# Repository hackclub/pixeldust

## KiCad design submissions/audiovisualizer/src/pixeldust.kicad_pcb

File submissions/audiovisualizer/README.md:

---
name: "Hridya Agrawal"
slack_id: "U0842GMRJKC"
github_handle: "@hridaya423"
---

# Audio Visualizer

⚠️ I would like to have 120 leds for the audio visualizer, so I would need a soldering iron.

Wokwi link: https://wokwi.com/projects/428497544685566977

This PCB captures audio from an I2S microphone and displays the frequency spectrum on a 120-LEDs. It uses FFT to adjust the LED brightness based on the audio data.

## BOM

| Comment           | Footprint                                      | Quantity 
|-------------------|------------------------------------------------|----------|
| WS2812B           | LED_SMD:LED_WS2812B_PLCC4_5.0x5.0mm_P3.2mm     | 120      |
| ICS-43434         | Sensor_Audio:InvenSense_ICS-43434-6_3.5x2.65mm | 1        |
| XIAO-RP2040-DIP   |Seeed Studio XIAO Series Library:XIAO-RP2040-DIP| 1        |

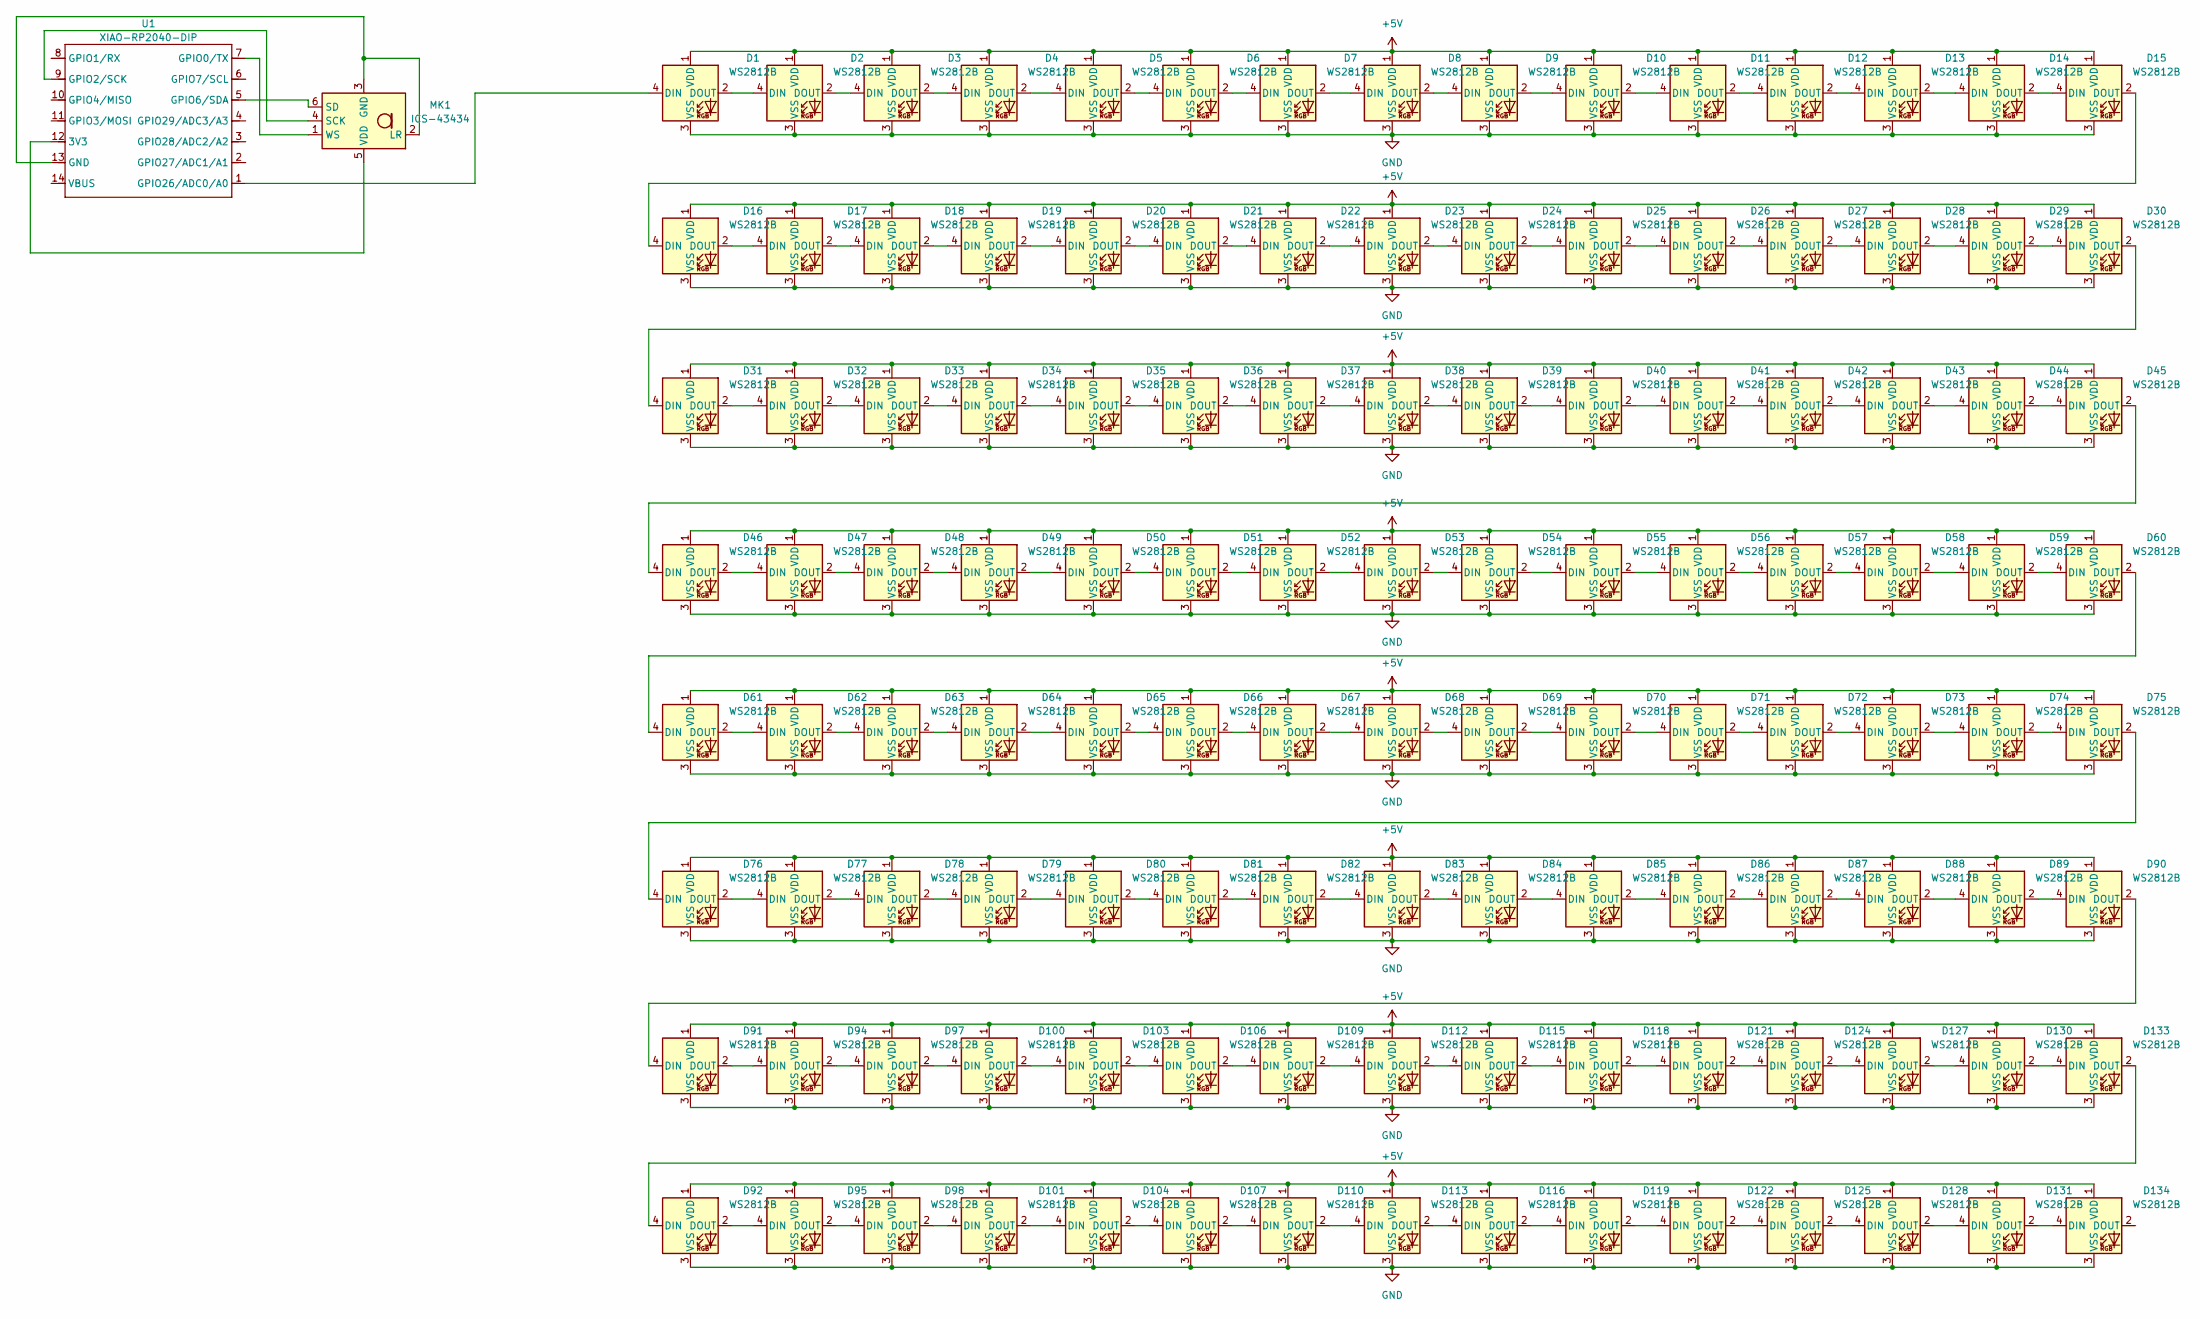
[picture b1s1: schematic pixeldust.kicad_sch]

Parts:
D1, D2, D3, D4, D5, D6, D7, D8, D9, D10, D11, D12, D13, D14, D15, D16, D17, D18, D19, D20, D21, D22, D23, D24, D25, D26, D27, D28, D29, D30, D31, D32, D33, D34, D35, D36, D37, D38, D39, D40, D41, D42, D43, D44, D45, D46, D47, D48, D49, D50, D51, D52, D53, D54, D55, D56, D57, D58, D59, D60, D61, D62, D63, D64, D65, D66, D67, D68, D69, D70, D71, D72, D73, D74, D75, D76, D77, D78, D79, D80, D81, D82, D83, D84, D85, D86, D87, D88, D89, D90, D91, D92, D94, D95, D97, D98, D100, D101, D103, D104, D106, D107, D109, D110, D112, D113, D115, D116, D118, D119, D121, D122, D124, D125, D127, D128, D130, D131, D133, D134: WS2812B; LED_WS2812B_PLCC4_5.0x5.0mm_P3.2mm
MK1: ICS-43434; InvenSense_ICS-43434-6_3.5x2.65mm
U1: XIAO-RP2040-DIP

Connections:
+5V: D1.1 (VDD), D2.1 (VDD), D3.1 (VDD), D4.1 (VDD), D5.1 (VDD), D6.1 (VDD), D7.1 (VDD), D8.1 (VDD), D9.1 (VDD), D10.1 (VDD), D11.1 (VDD), D12.1 (VDD), D13.1 (VDD), D14.1 (VDD), D15.1 (VDD), D16.1 (VDD), D17.1 (VDD), D18.1 (VDD), D19.1 (VDD), D20.1 (VDD), D21.1 (VDD), D22.1 (VDD), D23.1 (VDD), D24.1 (VDD), D25.1 (VDD), D26.1 (VDD), D27.1 (VDD), D28.1 (VDD), D29.1 (VDD), D30.1 (VDD), D31.1 (VDD), D32.1 (VDD), D33.1 (VDD), D34.1 (VDD), D35.1 (VDD), D36.1 (VDD), D37.1 (VDD), D38.1 (VDD), D39.1 (VDD), D40.1 (VDD), D41.1 (VDD), D42.1 (VDD), D43.1 (VDD), D44.1 (VDD), D45.1 (VDD), D46.1 (VDD), D47.1 (VDD), D48.1 (VDD), D49.1 (VDD), D50.1 (VDD), D51.1 (VDD), D52.1 (VDD), D53.1 (VDD), D54.1 (VDD), D55.1 (VDD), D56.1 (VDD), D57.1 (VDD), D58.1 (VDD), D59.1 (VDD), D60.1 (VDD), D61.1 (VDD), D62.1 (VDD), D63.1 (VDD), D64.1 (VDD), D65.1 (VDD), D66.1 (VDD), D67.1 (VDD), D68.1 (VDD), D69.1 (VDD), D70.1 (VDD), D71.1 (VDD), D72.1 (VDD), D73.1 (VDD), D74.1 (VDD), D75.1 (VDD), D76.1 (VDD), D77.1 (VDD), D78.1 (VDD), D79.1 (VDD), D80.1 (VDD), D81.1 (VDD), D82.1 (VDD), D83.1 (VDD), D84.1 (VDD), D85.1 (VDD), D86.1 (VDD), D87.1 (VDD), D88.1 (VDD), D89.1 (VDD), D90.1 (VDD), D91.1 (VDD), D92.1 (VDD), D94.1 (VDD), D95.1 (VDD), D97.1 (VDD), D98.1 (VDD), D100.1 (VDD), D101.1 (VDD), D103.1 (VDD), D104.1 (VDD), D106.1 (VDD), D107.1 (VDD), D109.1 (VDD), D110.1 (VDD), D112.1 (VDD), D113.1 (VDD), D115.1 (VDD), D116.1 (VDD), D118.1 (VDD), D119.1 (VDD), D121.1 (VDD), D122.1 (VDD), D124.1 (VDD), D125.1 (VDD), D127.1 (VDD), D128.1 (VDD), D130.1 (VDD), D131.1 (VDD), D133.1 (VDD), D134.1 (VDD)
GND: D1.3 (VSS), D2.3 (VSS), D3.3 (VSS), D4.3 (VSS), D5.3 (VSS), D6.3 (VSS), D7.3 (VSS), D8.3 (VSS), D9.3 (VSS), D10.3 (VSS), D11.3 (VSS), D12.3 (VSS), D13.3 (VSS), D14.3 (VSS), D15.3 (VSS), D16.3 (VSS), D17.3 (VSS), D18.3 (VSS), D19.3 (VSS), D20.3 (VSS), D21.3 (VSS), D22.3 (VSS), D23.3 (VSS), D24.3 (VSS), D25.3 (VSS), D26.3 (VSS), D27.3 (VSS), D28.3 (VSS), D29.3 (VSS), D30.3 (VSS), D31.3 (VSS), D32.3 (VSS), D33.3 (VSS), D34.3 (VSS), D35.3 (VSS), D36.3 (VSS), D37.3 (VSS), D38.3 (VSS), D39.3 (VSS), D40.3 (VSS), D41.3 (VSS), D42.3 (VSS), D43.3 (VSS), D44.3 (VSS), D45.3 (VSS), D46.3 (VSS), D47.3 (VSS), D48.3 (VSS), D49.3 (VSS), D50.3 (VSS), D51.3 (VSS), D52.3 (VSS), D53.3 (VSS), D54.3 (VSS), D55.3 (VSS), D56.3 (VSS), D57.3 (VSS), D58.3 (VSS), D59.3 (VSS), D60.3 (VSS), D61.3 (VSS), D62.3 (VSS), D63.3 (VSS), D64.3 (VSS), D65.3 (VSS), D66.3 (VSS), D67.3 (VSS), D68.3 (VSS), D69.3 (VSS), D70.3 (VSS), D71.3 (VSS), D72.3 (VSS), D73.3 (VSS), D74.3 (VSS), D75.3 (VSS), D76.3 (VSS), D77.3 (VSS), D78.3 (VSS), D79.3 (VSS), D80.3 (VSS), D81.3 (VSS), D82.3 (VSS), D83.3 (VSS), D84.3 (VSS), D85.3 (VSS), D86.3 (VSS), D87.3 (VSS), D88.3 (VSS), D89.3 (VSS), D90.3 (VSS), D91.3 (VSS), D92.3 (VSS), D94.3 (VSS), D95.3 (VSS), D97.3 (VSS), D98.3 (VSS), D100.3 (VSS), D101.3 (VSS), D103.3 (VSS), D104.3 (VSS), D106.3 (VSS), D107.3 (VSS), D109.3 (VSS), D110.3 (VSS), D112.3 (VSS), D113.3 (VSS), D115.3 (VSS), D116.3 (VSS), D118.3 (VSS), D119.3 (VSS), D121.3 (VSS), D122.3 (VSS), D124.3 (VSS), D125.3 (VSS), D127.3 (VSS), D128.3 (VSS), D130.3 (VSS), D131.3 (VSS), D133.3 (VSS), D134.3 (VSS)
unnamed: D1.4 (DIN), U1.1 (GPIO26/ADC0/A0)
unnamed: D1.2 (DOUT), D2.4 (DIN)
unnamed: D2.2 (DOUT), D3.4 (DIN)
unnamed: D3.2 (DOUT), D4.4 (DIN)
unnamed: D4.2 (DOUT), D5.4 (DIN)
unnamed: D5.2 (DOUT), D6.4 (DIN)
unnamed: D6.2 (DOUT), D7.4 (DIN)
unnamed: D7.2 (DOUT), D8.4 (DIN)
unnamed: D8.2 (DOUT), D9.4 (DIN)
unnamed: D9.2 (DOUT), D10.4 (DIN)
unnamed: D10.2 (DOUT), D11.4 (DIN)
unnamed: D11.2 (DOUT), D12.4 (DIN)
unnamed: D12.2 (DOUT), D13.4 (DIN)
unnamed: D13.2 (DOUT), D14.4 (DIN)
unnamed: D14.2 (DOUT), D15.4 (DIN)
unnamed: D15.2 (DOUT), D16.4 (DIN)
unnamed: D16.2 (DOUT), D17.4 (DIN)
unnamed: D17.2 (DOUT), D18.4 (DIN)
unnamed: D18.2 (DOUT), D19.4 (DIN)
unnamed: D19.2 (DOUT), D20.4 (DIN)
unnamed: D20.2 (DOUT), D21.4 (DIN)
unnamed: D21.2 (DOUT), D22.4 (DIN)
unnamed: D22.2 (DOUT), D23.4 (DIN)
unnamed: D23.2 (DOUT), D24.4 (DIN)
unnamed: D24.2 (DOUT), D25.4 (DIN)
unnamed: D25.2 (DOUT), D26.4 (DIN)
unnamed: D26.2 (DOUT), D27.4 (DIN)
unnamed: D27.2 (DOUT), D28.4 (DIN)
unnamed: D28.2 (DOUT), D29.4 (DIN)
unnamed: D29.2 (DOUT), D30.4 (DIN)
unnamed: D30.2 (DOUT), D31.4 (DIN)
unnamed: D31.2 (DOUT), D32.4 (DIN)
unnamed: D32.2 (DOUT), D33.4 (DIN)
unnamed: D33.2 (DOUT), D34.4 (DIN)
unnamed: D34.2 (DOUT), D35.4 (DIN)
unnamed: D35.2 (DOUT), D36.4 (DIN)
unnamed: D36.2 (DOUT), D37.4 (DIN)
unnamed: D37.2 (DOUT), D38.4 (DIN)
unnamed: D38.2 (DOUT), D39.4 (DIN)
unnamed: D39.2 (DOUT), D40.4 (DIN)
unnamed: D40.2 (DOUT), D41.4 (DIN)
unnamed: D41.2 (DOUT), D42.4 (DIN)
unnamed: D42.2 (DOUT), D43.4 (DIN)
unnamed: D43.2 (DOUT), D44.4 (DIN)
unnamed: D44.2 (DOUT), D45.4 (DIN)
unnamed: D45.2 (DOUT), D46.4 (DIN)
unnamed: D46.2 (DOUT), D47.4 (DIN)
unnamed: D47.2 (DOUT), D48.4 (DIN)
unnamed: D48.2 (DOUT), D49.4 (DIN)
unnamed: D49.2 (DOUT), D50.4 (DIN)
unnamed: D50.2 (DOUT), D51.4 (DIN)
unnamed: D51.2 (DOUT), D52.4 (DIN)
unnamed: D52.2 (DOUT), D53.4 (DIN)
unnamed: D53.2 (DOUT), D54.4 (DIN)
unnamed: D54.2 (DOUT), D55.4 (DIN)
unnamed: D55.2 (DOUT), D56.4 (DIN)
unnamed: D56.2 (DOUT), D57.4 (DIN)
unnamed: D57.2 (DOUT), D58.4 (DIN)
unnamed: D58.2 (DOUT), D59.4 (DIN)
unnamed: D59.2 (DOUT), D60.4 (DIN)
unnamed: D60.2 (DOUT), D61.4 (DIN)
unnamed: D61.2 (DOUT), D62.4 (DIN)
unnamed: D62.2 (DOUT), D63.4 (DIN)
unnamed: D63.2 (DOUT), D64.4 (DIN)
unnamed: D64.2 (DOUT), D65.4 (DIN)
unnamed: D65.2 (DOUT), D66.4 (DIN)
unnamed: D66.2 (DOUT), D67.4 (DIN)
unnamed: D67.2 (DOUT), D68.4 (DIN)
unnamed: D68.2 (DOUT), D69.4 (DIN)
unnamed: D69.2 (DOUT), D70.4 (DIN)
unnamed: D70.2 (DOUT), D71.4 (DIN)
unnamed: D71.2 (DOUT), D72.4 (DIN)
unnamed: D72.2 (DOUT), D73.4 (DIN)
unnamed: D73.2 (DOUT), D74.4 (DIN)
unnamed: D74.2 (DOUT), D75.4 (DIN)
unnamed: D75.2 (DOUT), D76.4 (DIN)
unnamed: D76.2 (DOUT), D77.4 (DIN)
unnamed: D77.2 (DOUT), D78.4 (DIN)
unnamed: D78.2 (DOUT), D79.4 (DIN)
unnamed: D79.2 (DOUT), D80.4 (DIN)
unnamed: D80.2 (DOUT), D81.4 (DIN)
unnamed: D81.2 (DOUT), D82.4 (DIN)
unnamed: D82.2 (DOUT), D83.4 (DIN)
unnamed: D83.2 (DOUT), D84.4 (DIN)
unnamed: D84.2 (DOUT), D85.4 (DIN)
unnamed: D85.2 (DOUT), D86.4 (DIN)
unnamed: D86.2 (DOUT), D87.4 (DIN)
unnamed: D87.2 (DOUT), D88.4 (DIN)
unnamed: D88.2 (DOUT), D89.4 (DIN)
unnamed: D89.2 (DOUT), D90.4 (DIN)
unnamed: D90.2 (DOUT), D91.4 (DIN)
unnamed: D91.2 (DOUT), D94.4 (DIN)
unnamed: D92.2 (DOUT), D95.4 (DIN)
unnamed: D94.2 (DOUT), D97.4 (DIN)
unnamed: D95.2 (DOUT), D98.4 (DIN)
unnamed: D97.2 (DOUT), D100.4 (DIN)
unnamed: D100.2 (DOUT), D103.4 (DIN)
unnamed: D98.2 (DOUT), D101.4 (DIN)
unnamed: D101.2 (DOUT), D104.4 (DIN)
unnamed: D103.2 (DOUT), D106.4 (DIN)
unnamed: D104.2 (DOUT), D107.4 (DIN)
unnamed: D106.2 (DOUT), D109.4 (DIN)
unnamed: D107.2 (DOUT), D110.4 (DIN)
unnamed: D109.2 (DOUT), D112.4 (DIN)
unnamed: D110.2 (DOUT), D113.4 (DIN)
unnamed: D112.2 (DOUT), D115.4 (DIN)
unnamed: D113.2 (DOUT), D116.4 (DIN)
unnamed: D115.2 (DOUT), D118.4 (DIN)
unnamed: D116.2 (DOUT), D119.4 (DIN)
unnamed: D118.2 (DOUT), D121.4 (DIN)
unnamed: D119.2 (DOUT), D122.4 (DIN)
unnamed: D121.2 (DOUT), D124.4 (DIN)
unnamed: D122.2 (DOUT), D125.4 (DIN)
unnamed: D124.2 (DOUT), D127.4 (DIN)
unnamed: D125.2 (DOUT), D128.4 (DIN)
unnamed: D127.2 (DOUT), D130.4 (DIN)
unnamed: D128.2 (DOUT), D131.4 (DIN)
unnamed: D130.2 (DOUT), D133.4 (DIN)
unnamed: D131.2 (DOUT), D134.4 (DIN)
unnamed: D92.4 (DIN), D133.2 (DOUT)
unnamed: MK1.2 (LR), MK1.3 (GND), U1.13 (GND)
unnamed: MK1.4 (SCK), U1.9 (GPIO2/SCK)
unnamed: MK1.6 (SD), U1.5 (GPIO6/SDA)
unnamed: MK1.5 (VDD), U1.12 (3V3)
unnamed: MK1.1 (WS), U1.7 (GPIO0/TX)

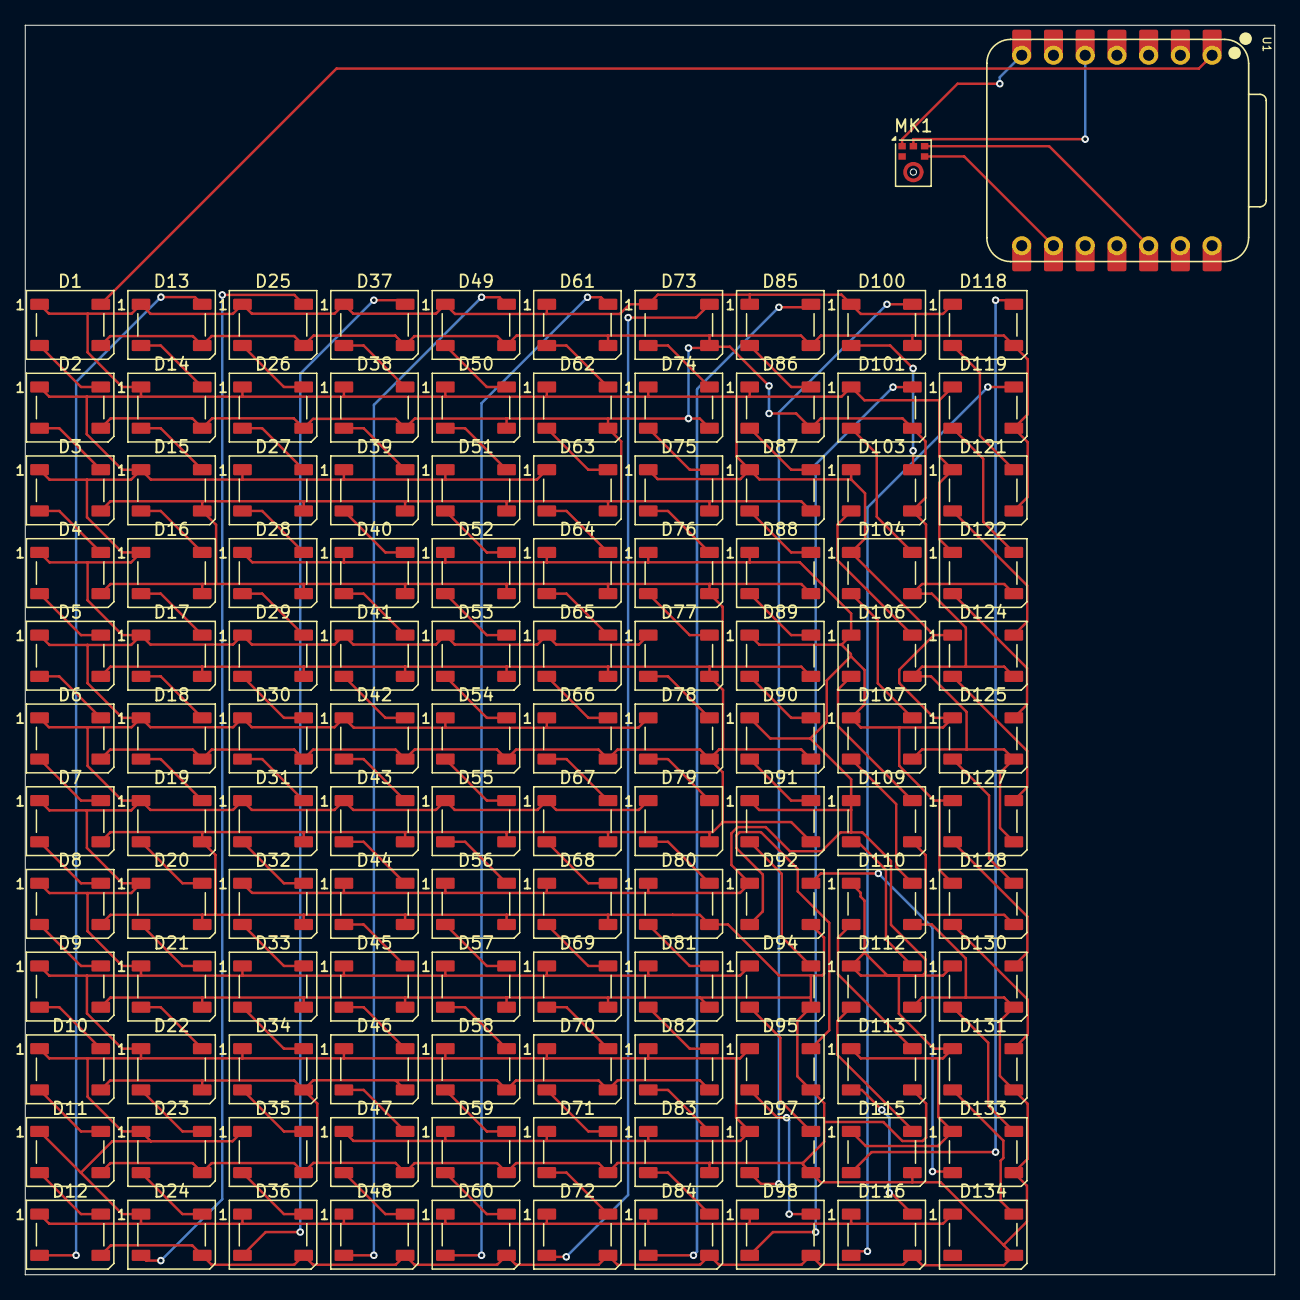
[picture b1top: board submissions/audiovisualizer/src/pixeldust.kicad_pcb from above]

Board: 2 copper layers, 100.0 x 100.0 mm, 122 parts (0 on the bottom side), 127 nets.

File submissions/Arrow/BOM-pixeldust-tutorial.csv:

Comment,Footprint,Quantity,LCSC
100uF,C_1206_3216Metric_Pad1.33x1.80mm_HandSolder,1,C15008
4.7nF,C_0402_1005Metric_Pad0.74x0.62mm_HandSolder,3,C1538
WS2812B,LED_WS2812B_PLCC4_5.0x5.0mm_P3.2mm,9,
XIAO-RP2040-DIP,XIAO-RP2040-DIP,1,
SW_Push,SW_Cherry_MX_1.00u_PCB,2,

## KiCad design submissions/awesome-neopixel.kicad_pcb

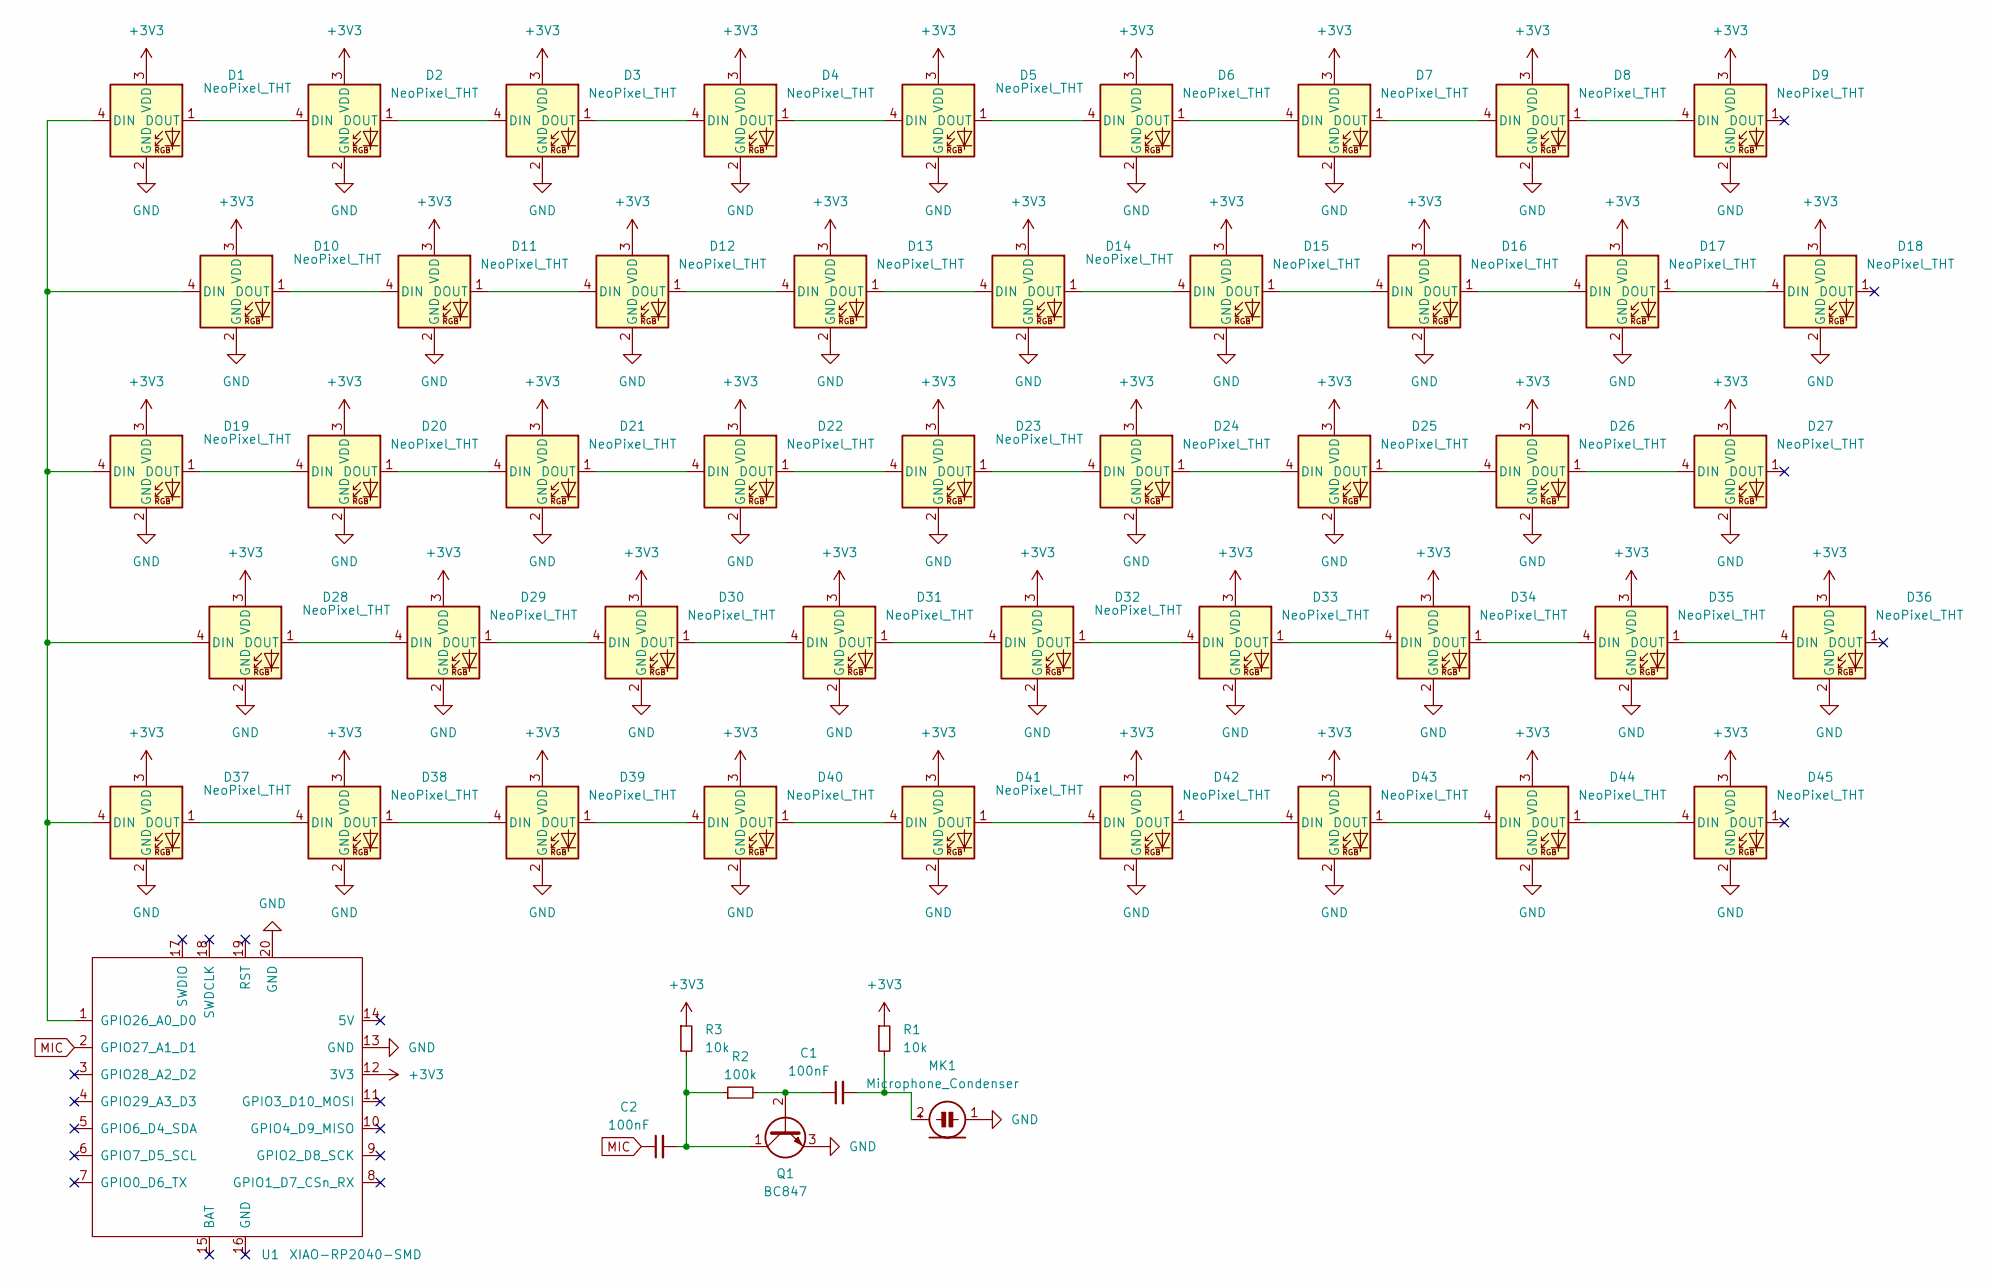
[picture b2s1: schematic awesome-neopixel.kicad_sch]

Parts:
C1, C2: 100nF; C_0603_1608Metric
D1, D2, D3, D4, D5, D6, D7, D8, D9, D10, D11, D12, D13, D14, D15, D16, D17, D18, D19, D20, D21, D22, D23, D24, D25, D26, D27, D28, D29, D30, D31, D32, D33, D34, D35, D36, D37, D38, D39, D40, D41, D42, D43, D44, D45: NeoPixel_THT; LED_WS2812B_PLCC4_5.0x5.0mm_P3.2mm
MK1: Microphone_Condenser; CUI_CMC-4013-SMT
Q1: BC847; SOT-23
R1, R3: 10k; R_0603_1608Metric
R2: 100k; R_0805_2012Metric
U1: XIAO-RP2040-SMD

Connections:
GND: D1.2 (GND), D2.2 (GND), D3.2 (GND), D4.2 (GND), D5.2 (GND), D6.2 (GND), D7.2 (GND), D8.2 (GND), D9.2 (GND), D10.2 (GND), D11.2 (GND), D12.2 (GND), D13.2 (GND), D14.2 (GND), D15.2 (GND), D16.2 (GND), D17.2 (GND), D18.2 (GND), D19.2 (GND), D20.2 (GND), D21.2 (GND), D22.2 (GND), D23.2 (GND), D24.2 (GND), D25.2 (GND), D26.2 (GND), D27.2 (GND), D28.2 (GND), D29.2 (GND), D30.2 (GND), D31.2 (GND), D32.2 (GND), D33.2 (GND), D34.2 (GND), D35.2 (GND), D36.2 (GND), D37.2 (GND), D38.2 (GND), D39.2 (GND), D40.2 (GND), D41.2 (GND), D42.2 (GND), D43.2 (GND), D44.2 (GND), D45.2 (GND), MK1.1 (-), Q1.3 (E), U1.13 (GND), U1.20 (GND)
MIC: C2.1, U1.2 (GPIO27_A1_D1)
unnamed: D1.4 (DIN), D10.4 (DIN), D19.4 (DIN), D28.4 (DIN), D37.4 (DIN), U1.1 (GPIO26_A0_D0)
unnamed: D1.1 (DOUT), D2.4 (DIN)
unnamed: D2.1 (DOUT), D3.4 (DIN)
unnamed: D3.1 (DOUT), D4.4 (DIN)
unnamed: D4.1 (DOUT), D5.4 (DIN)
unnamed: D5.1 (DOUT), D6.4 (DIN)
unnamed: D6.1 (DOUT), D7.4 (DIN)
unnamed: D7.1 (DOUT), D8.4 (DIN)
unnamed: D8.1 (DOUT), D9.4 (DIN)
unnamed: D10.1 (DOUT), D11.4 (DIN)
unnamed: D11.1 (DOUT), D12.4 (DIN)
unnamed: D12.1 (DOUT), D13.4 (DIN)
unnamed: D13.1 (DOUT), D14.4 (DIN)
unnamed: D14.1 (DOUT), D15.4 (DIN)
unnamed: D15.1 (DOUT), D16.4 (DIN)
unnamed: D16.1 (DOUT), D17.4 (DIN)
unnamed: D17.1 (DOUT), D18.4 (DIN)
unnamed: D19.1 (DOUT), D20.4 (DIN)
unnamed: D20.1 (DOUT), D21.4 (DIN)
unnamed: D21.1 (DOUT), D22.4 (DIN)
unnamed: D22.1 (DOUT), D23.4 (DIN)
unnamed: D23.1 (DOUT), D24.4 (DIN)
unnamed: D24.1 (DOUT), D25.4 (DIN)
unnamed: D25.1 (DOUT), D26.4 (DIN)
unnamed: D26.1 (DOUT), D27.4 (DIN)
unnamed: D28.1 (DOUT), D29.4 (DIN)
unnamed: D29.1 (DOUT), D30.4 (DIN)
unnamed: D30.1 (DOUT), D31.4 (DIN)
unnamed: D31.1 (DOUT), D32.4 (DIN)
unnamed: D32.1 (DOUT), D33.4 (DIN)
unnamed: D33.1 (DOUT), D34.4 (DIN)
unnamed: D34.1 (DOUT), D35.4 (DIN)
unnamed: D35.1 (DOUT), D36.4 (DIN)
unnamed: D37.1 (DOUT), D38.4 (DIN)
unnamed: D38.1 (DOUT), D39.4 (DIN)
unnamed: D39.1 (DOUT), D40.4 (DIN)
unnamed: D40.1 (DOUT), D41.4 (DIN)
unnamed: D41.1 (DOUT), D42.4 (DIN)
unnamed: D42.1 (DOUT), D43.4 (DIN)
unnamed: D43.1 (DOUT), D44.4 (DIN)
unnamed: D44.1 (DOUT), D45.4 (DIN)
unnamed: C1.1, Q1.2 (B), R2.2
unnamed: C2.2, Q1.1 (C), R2.1, R3.2

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
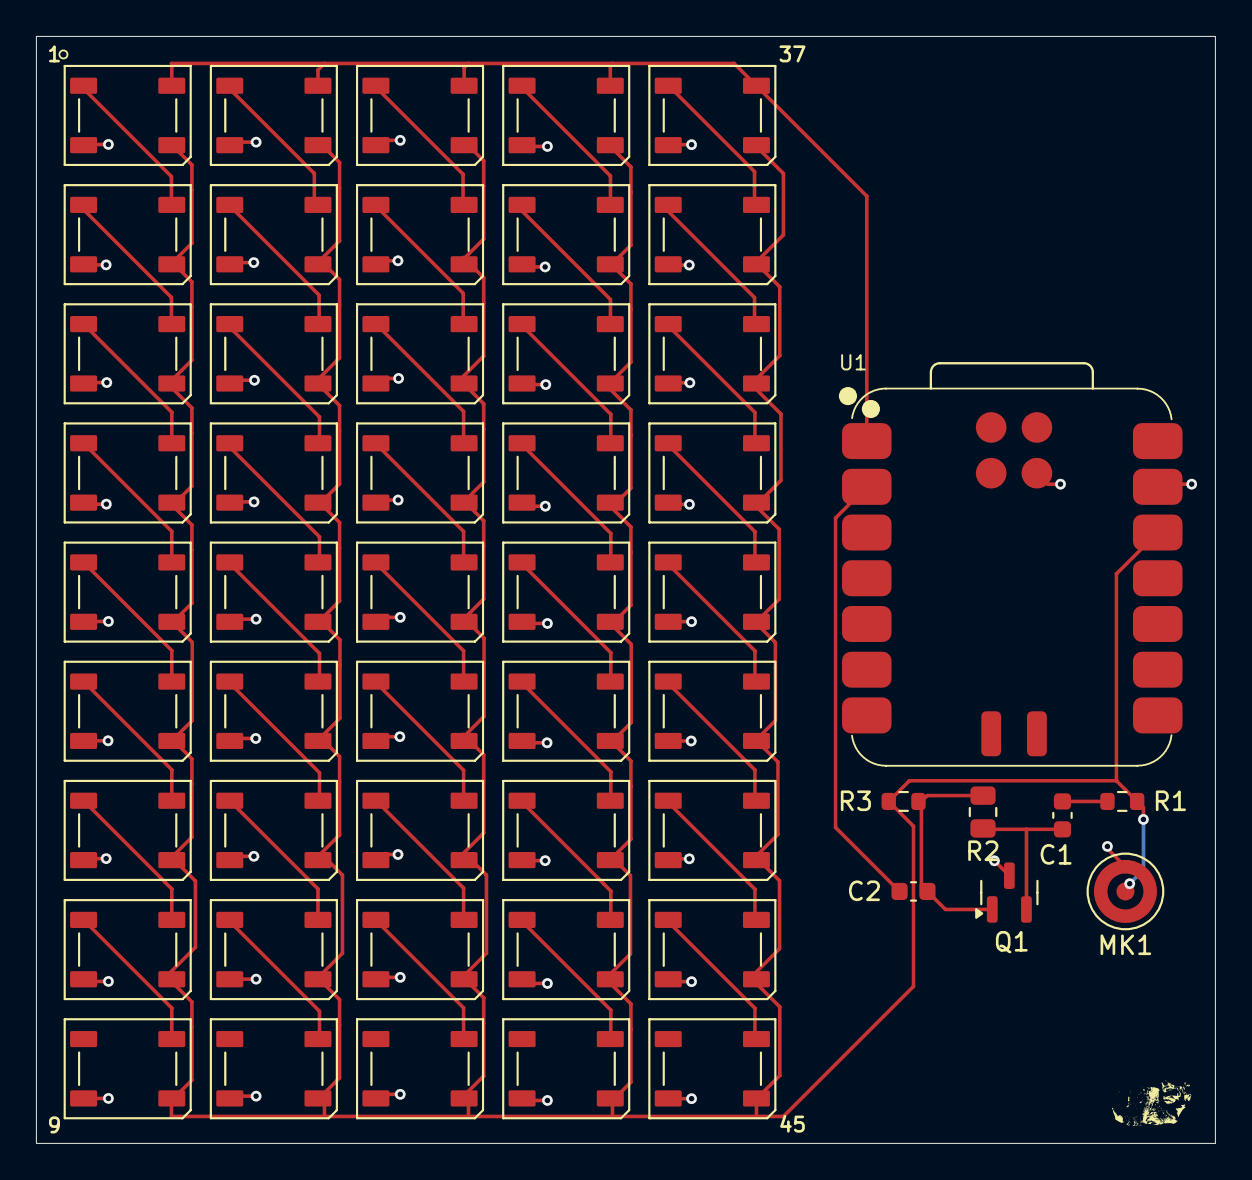
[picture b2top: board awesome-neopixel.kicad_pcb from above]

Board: 2 copper layers, 65.5 x 61.5 mm, 54 parts (0 on the bottom side), 47 nets.

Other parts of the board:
Intimidator: LOGO; timmy2

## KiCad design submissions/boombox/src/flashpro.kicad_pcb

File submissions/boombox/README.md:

---
slack_id: "U07CXLNF1JS"
github_handle: "@JavaScythe"
wokwi: https://wokwi.com/projects/428017058956591105
---

# boombox

Replace the wokwi link below with yours

Wokwi link: [https://wokwi.com/projects/428017058956591105](https://wokwi.com/projects/428017058956591105)

<!-- Uncomment the line below if you need a soldering iron -->
⚠️ I don't want to solder my neopixels, but since I am above the 50 limit, I would need ONLY soldering assesories if possible, as I already have an iron. 

Boombox intends to make use of the minimum of 5 pcbs printed by JLCPCB by ensuring the design can be fit together to form one large board, in this case the shape of a box. It is intended to be hung and be used as an audio visualizer under OpenRGB using the E1.31 protocol.

A simplified BOM table
(pls include rough pricing of any extra components you're using)

<!-- Example: -->

| Comment           | Footprint                                      | Quantity | LCSC     | Cost   |
|-------------------|------------------------------------------------|----------|----------|--------|
| SK6812            | LED_SK6812_PLCC4_5.0x5.0mm_P3.2mm              | 130      |          |        |
| 90Deg Pin Header  | PinHeader_1x03_P2.54mm_Horizontal              | 10       | C92159   | $0.37  |
| Pin Header        | PinHeader_1x0N_P2.54mm_Vertical                | 50       |  Any combination to make 10x 3pin and 10x 2pin
| 5v to 3.3v        | PinHeader_1x03_P2.54mm_Vertical                | 1        |  3 Pins AMS1117| 0.72 for 5   |
| 2x4 Female Pin H. |                                                | 1x       | C41427526| $1.36  |

Tell us a little bit about your design process. What were some challenges? What helped?

I wanted to make a room scale audio visualizer, and needed the maximum PCB area to make it effective, as well as varying directions for the leds. The square design is optimal and easy to make.

It works by exposing two pin headers to disconnect either of the blue wires in the schematic below
This allows me to connect a path across the cube's faces for the data pins. Power is distributed throughout through ground fills on both sides of each face.

Finally, the whole thing will be controlled by a ESP-01 powered from the voltage step down. It will run a E1.31 server to recieve lighting instructions from OpenRGB.

The tiny 7-neopixel circle I have already is bright and crisp, I can only imagine how epic the final product will be.

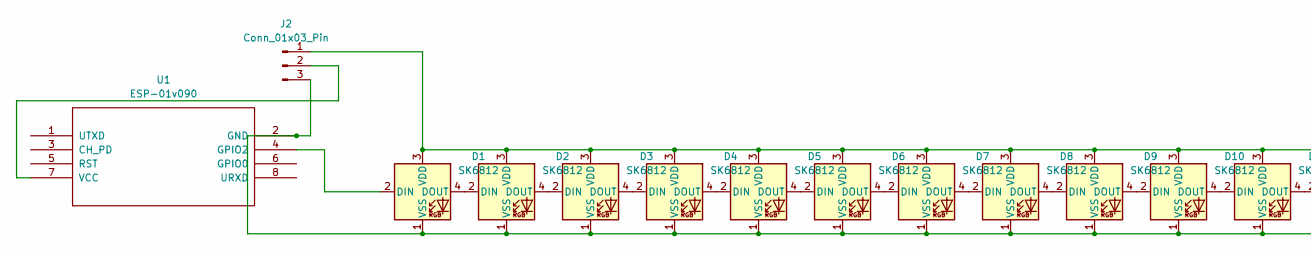
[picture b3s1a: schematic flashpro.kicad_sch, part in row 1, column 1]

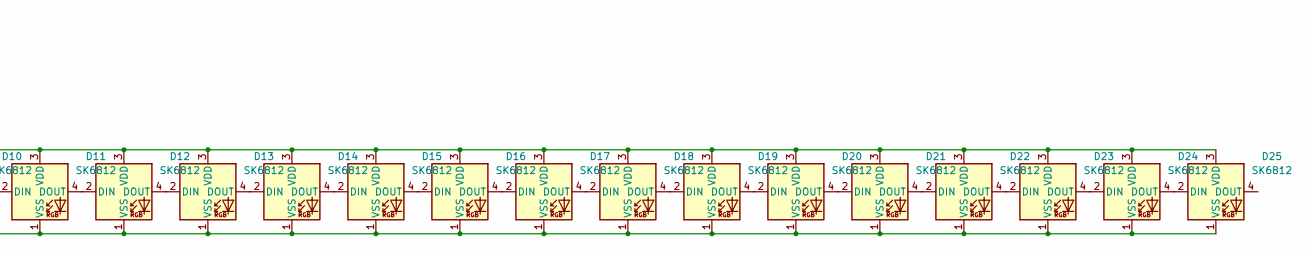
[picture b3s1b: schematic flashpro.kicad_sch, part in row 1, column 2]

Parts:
D1, D2, D3, D4, D5, D6, D7, D8, D9, D10, D11, D12, D13, D14, D15, D16, D17, D18, D19, D20, D21, D22, D23, D24, D25: SK6812; LED_SK6812_PLCC4_5.0x5.0mm_P3.2mm
J2: Conn_01x03_Pin; PinHeader_1x03_P2.54mm_Vertical
U1: ESP-01v090; ESP-01

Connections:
unnamed: D1.2 (DIN), U1.4 (GPIO2)
unnamed: D1.4 (DOUT), D2.2 (DIN)
unnamed 2: D1.3 (VDD), D2.3 (VDD), D3.3 (VDD), D4.3 (VDD), D5.3 (VDD), D6.3 (VDD), D7.3 (VDD), D8.3 (VDD), D9.3 (VDD), D10.3 (VDD), D11.3 (VDD), D12.3 (VDD), D13.3 (VDD), D14.3 (VDD), D15.3 (VDD), D16.3 (VDD), D17.3 (VDD), D18.3 (VDD), D19.3 (VDD), D20.3 (VDD), D21.3 (VDD), D22.3 (VDD), D23.3 (VDD), D24.3 (VDD), D25.3 (VDD), J2.1; also elsewhere on the board
unnamed 3: D1.1 (VSS), D2.1 (VSS), D3.1 (VSS), D4.1 (VSS), D5.1 (VSS), D6.1 (VSS), D7.1 (VSS), D8.1 (VSS), D9.1 (VSS), D10.1 (VSS), D11.1 (VSS), D12.1 (VSS), D13.1 (VSS), D14.1 (VSS), D15.1 (VSS), D16.1 (VSS), D17.1 (VSS), D18.1 (VSS), D19.1 (VSS), D20.1 (VSS), D21.1 (VSS), D22.1 (VSS), D23.1 (VSS), D24.1 (VSS), D25.1 (VSS), J2.3, U1.2 (GND); also elsewhere on the board
unnamed: D2.4 (DOUT), D3.2 (DIN)
unnamed: D3.4 (DOUT), D4.2 (DIN)
unnamed: D4.4 (DOUT), D5.2 (DIN)
unnamed: D5.4 (DOUT), D6.2 (DIN)
unnamed: D6.4 (DOUT), D7.2 (DIN)
unnamed: D7.4 (DOUT), D8.2 (DIN)
unnamed: D8.4 (DOUT), D9.2 (DIN)
unnamed: D9.4 (DOUT), D10.2 (DIN)
unnamed: D10.4 (DOUT), D11.2 (DIN)
unnamed: D11.4 (DOUT), D12.2 (DIN)
unnamed: D12.4 (DOUT), D13.2 (DIN)
unnamed: D13.4 (DOUT), D14.2 (DIN)
unnamed: D14.4 (DOUT), D15.2 (DIN)
unnamed: D15.4 (DOUT), D16.2 (DIN)
unnamed: D16.4 (DOUT), D17.2 (DIN)
unnamed: D17.4 (DOUT), D18.2 (DIN)
unnamed: D18.4 (DOUT), D19.2 (DIN)
unnamed: D19.4 (DOUT), D20.2 (DIN)
unnamed: D20.4 (DOUT), D21.2 (DIN)
unnamed: D21.4 (DOUT), D22.2 (DIN)
unnamed: D22.4 (DOUT), D23.2 (DIN)
unnamed: D23.4 (DOUT), D24.2 (DIN)
unnamed: D24.4 (DOUT), D25.2 (DIN)
unnamed: J2.2, U1.7 (VCC)

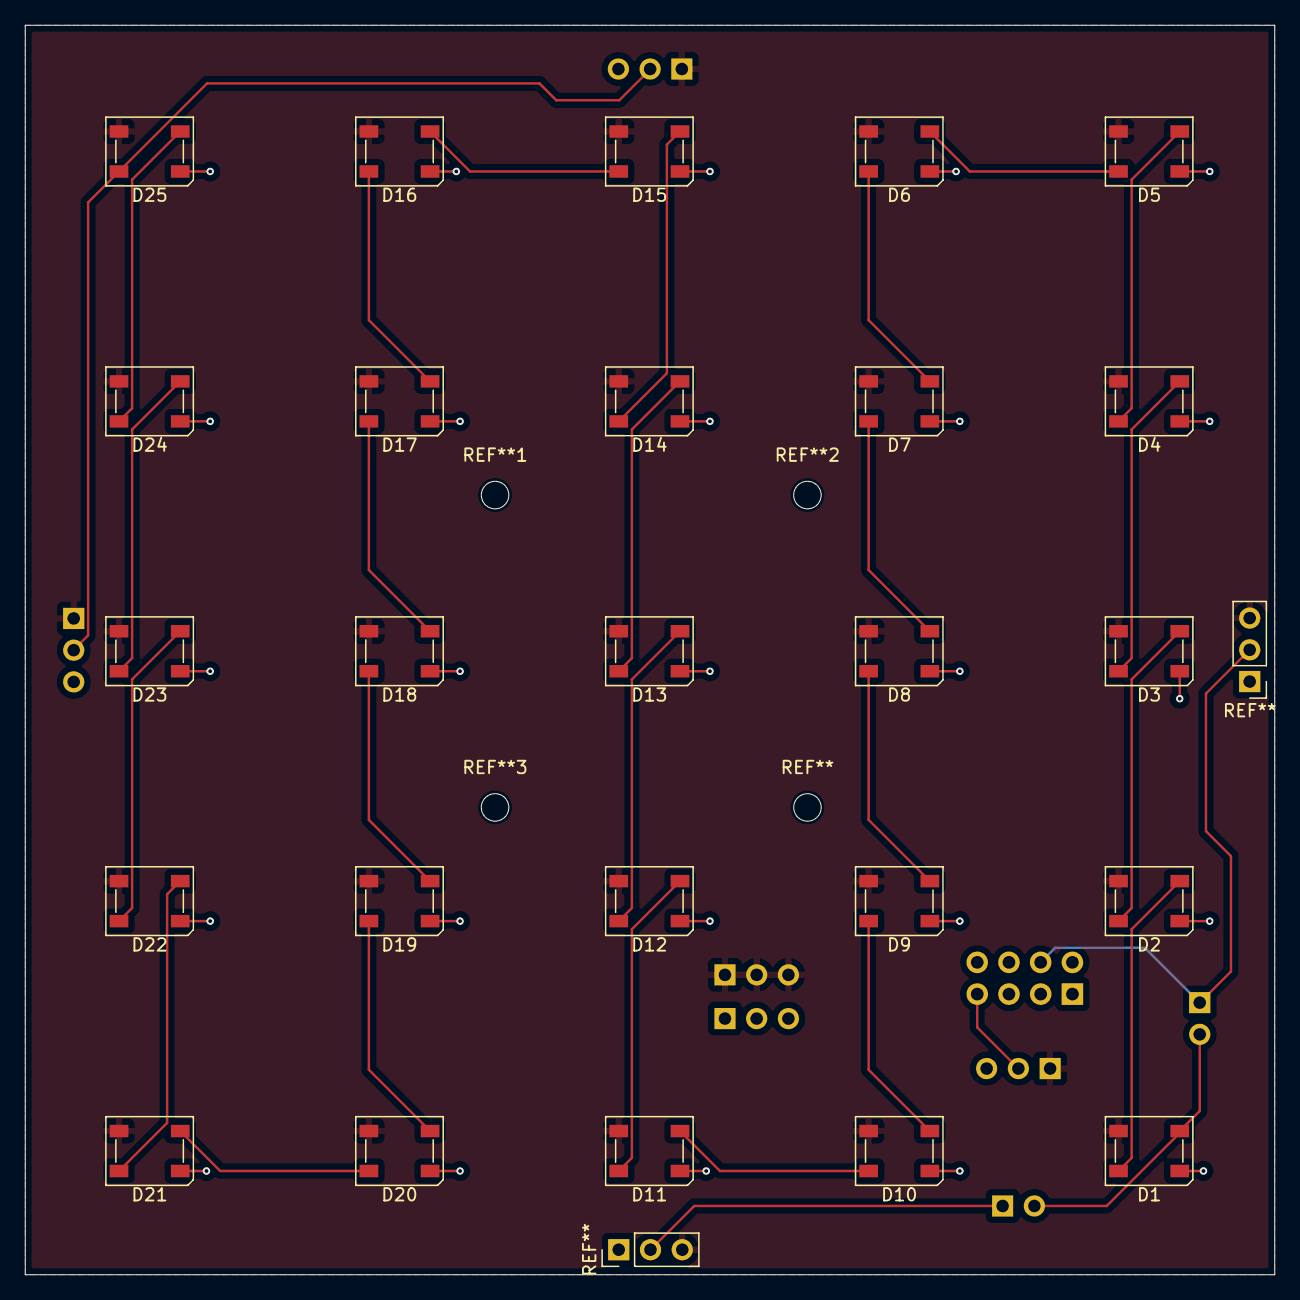
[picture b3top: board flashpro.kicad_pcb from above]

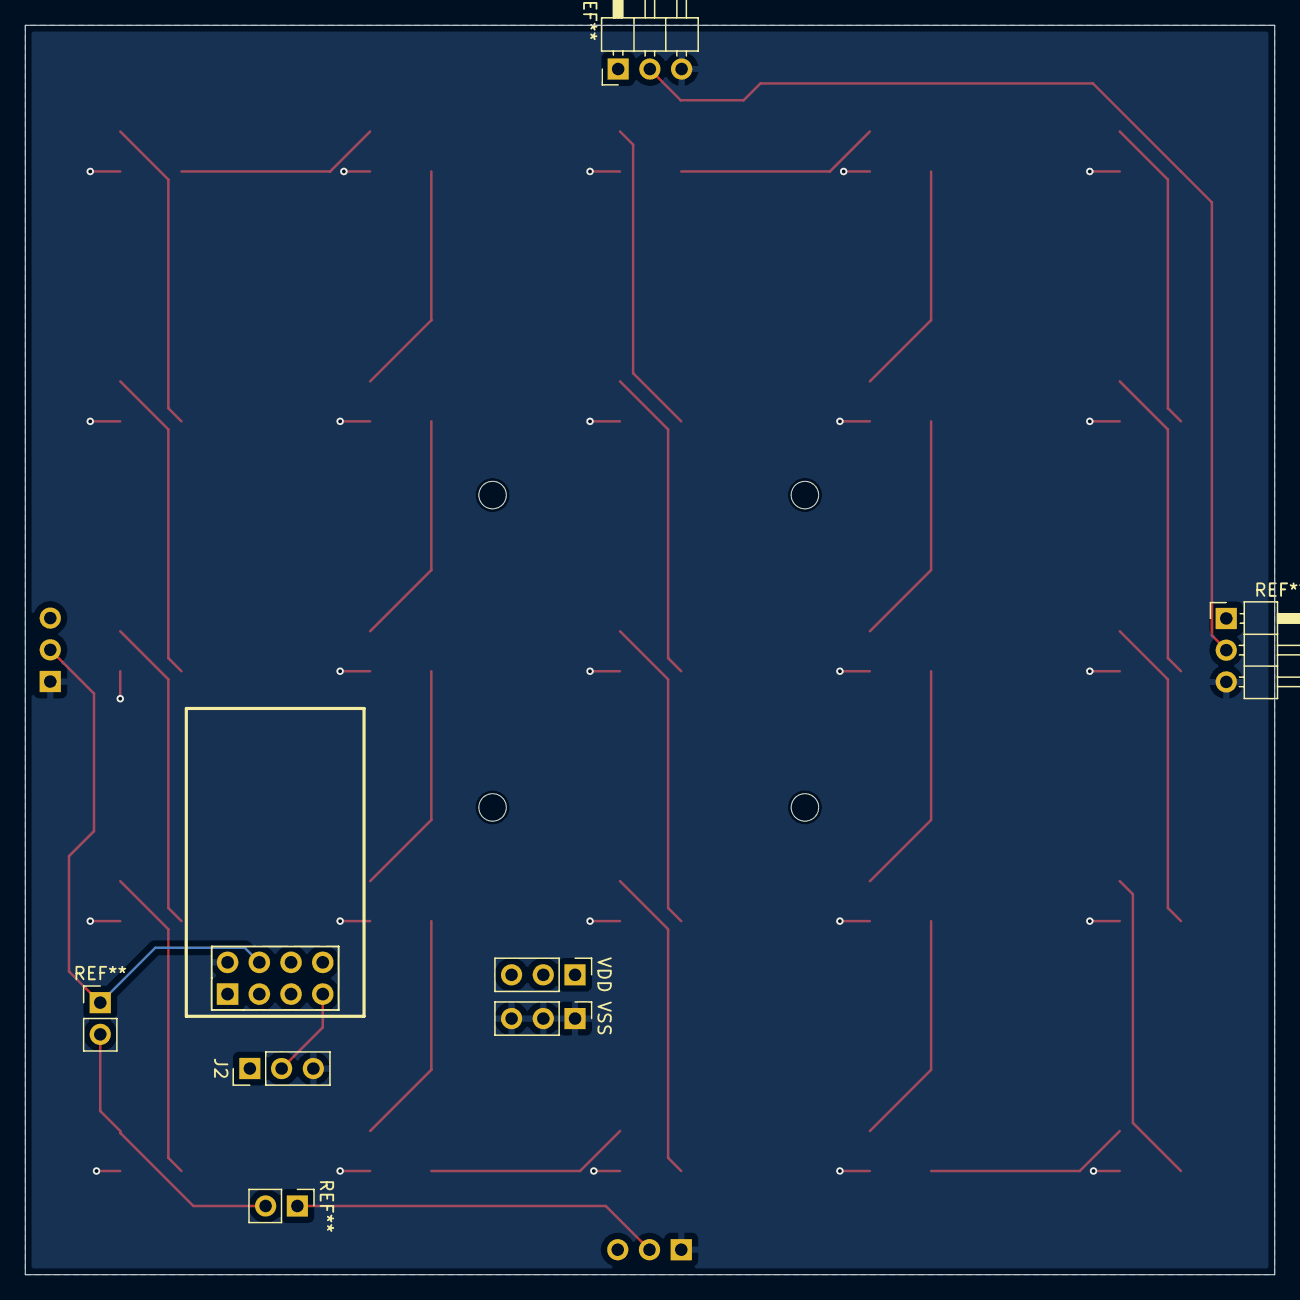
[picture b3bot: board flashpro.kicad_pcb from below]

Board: 2 copper layers, 100.0 x 100.0 mm, 29 parts (4 on the bottom side), 28 nets.

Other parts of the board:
VDD: PinHeader_1x03_P2.54mm_Vertical
VSS: PinHeader_1x03_P2.54mm_Vertical

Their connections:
unnamed 2: VDD.1, VDD.2, VDD.3; also elsewhere on the board
unnamed 3: VSS.1, VSS.2, VSS.3; also elsewhere on the board

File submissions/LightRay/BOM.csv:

"Reference","Value","Footprint","Datasheet","Qty","DNP","Exclude from BOM","Exclude from Board"
"C1","100uF","Capacitor_SMD:C_1210_3225Metric_Pad1.33x2.70mm_HandSolder","~","1","","",""
"C2,C3,C4","4.7nF","Capacitor_SMD:C_1206_3216Metric_Pad1.33x1.80mm_HandSolder","~","3","","",""
"D1,D2,D3,D4,D5,D6,D7,D8,D9,D10,D11,D12,D13,D14,D15","WS2812B","LED_SMD:LED_WS2812B_PLCC4_5.0x5.0mm_P3.2mm","https://cdn-shop.adafruit.com/datasheets/WS2812B.pdf","15","","",""
"SW1","RotaryEncoder_Switch","Rotary_Encoder:RotaryEncoder_Alps_EC11E-Switch_Vertical_H20mm","~","1","","",""
"SW2,SW3","SW_Push","Button_Switch_Keyboard:SW_Cherry_MX_1.00u_PCB","~","2","","",""
"U1","XIAO-RP2040-SMD","OPL:XIAO-RP2040-SMD","","1","","",""
